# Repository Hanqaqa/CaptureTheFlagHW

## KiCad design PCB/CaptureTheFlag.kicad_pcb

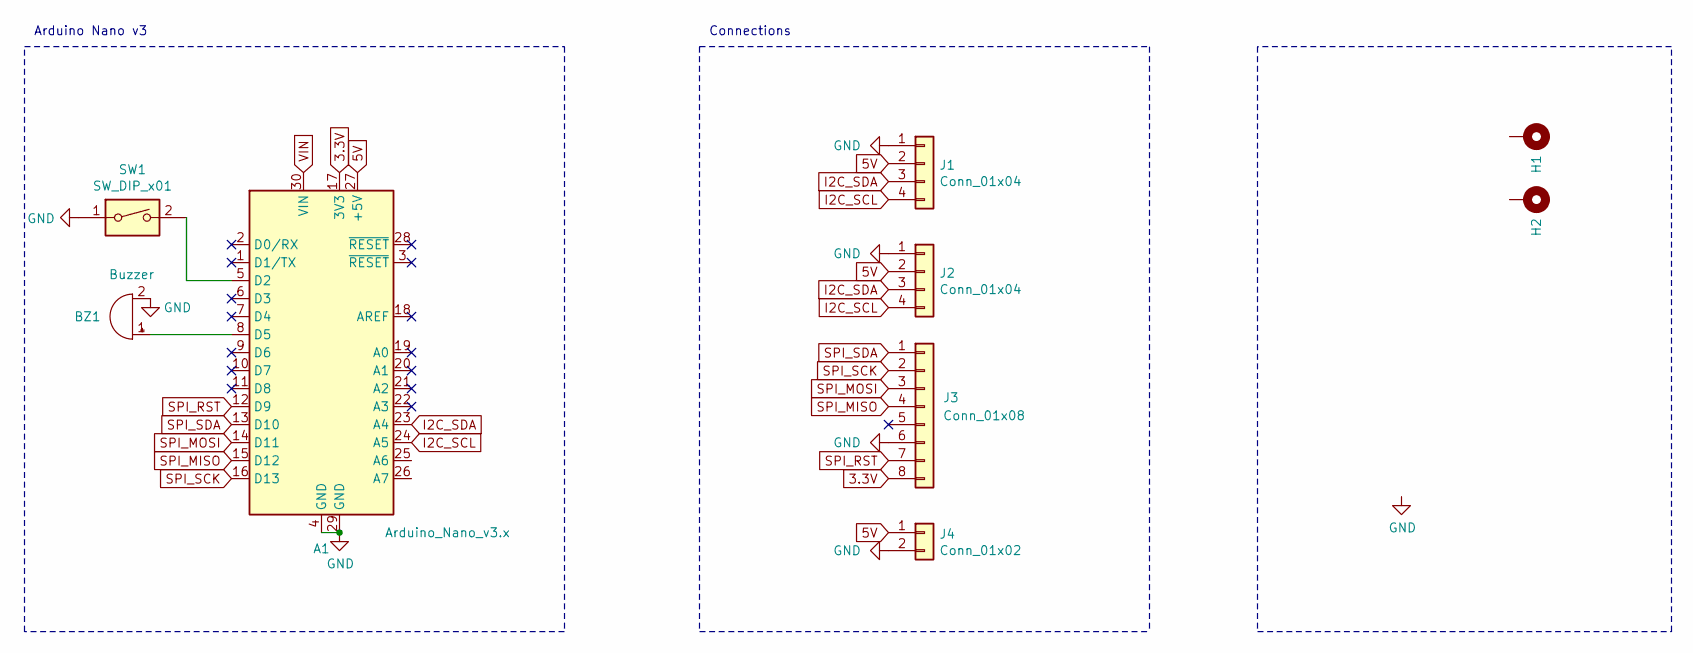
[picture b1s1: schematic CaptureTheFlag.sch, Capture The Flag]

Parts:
A1: Arduino_Nano_v3.x; Arduino_Nano
BZ1: Buzzer; Buzzer_12x9.5RM7.6
H1, H2: MountingHole_Pad; MountingHole_3.2mm_M3
J1, J2: Conn_01x04; PinHeader_1x04_P2.54mm_Vertical
J3: Conn_01x08; PinHeader_1x08_P2.54mm_Vertical
J4: Conn_01x02; PinHeader_1x02_P2.54mm_Vertical
SW1: SW_DIP_x01; PinHeader_1x02_P2.54mm_Vertical

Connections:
3.3V: A1.17 (3V3), J3.8
5V: A1.27 (+5V), J1.2, J2.2, J4.1
GND: A1.4 (GND), A1.29 (GND), BZ1.2 (+), J1.1, J2.1, J3.6, J4.2, SW1.1
I2C_SCL: A1.24 (A5), J1.4, J2.4
I2C_SDA: A1.23 (A4), J1.3, J2.3
unnamed: A1.5 (D2), SW1.2
unnamed: A1.8 (D5), BZ1.1 (-)
SPI_MISO: A1.15 (D12), J3.4
SPI_MOSI: A1.14 (D11), J3.3
SPI_RST: A1.12 (D9), J3.7
SPI_SCK: A1.16 (D13), J3.2
SPI_SDA: A1.13 (D10), J3.1
VIN: A1.30 (VIN)

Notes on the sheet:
Arduino Nano v3
Connections

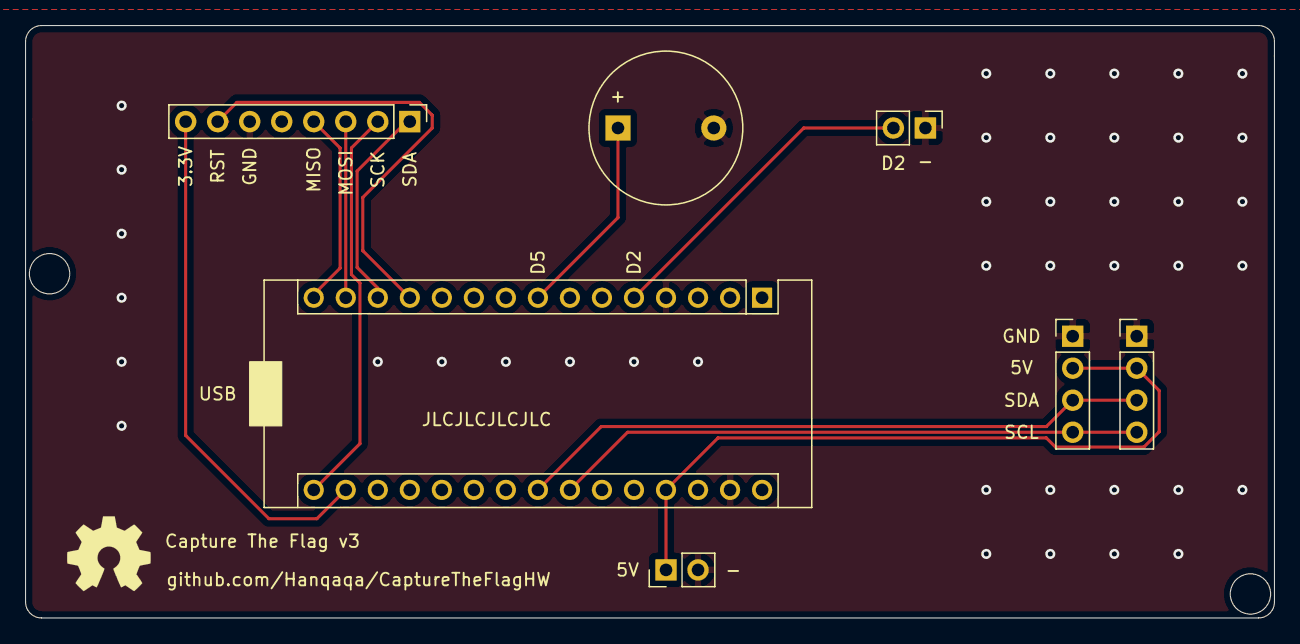
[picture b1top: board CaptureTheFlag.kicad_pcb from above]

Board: 2 copper layers, 99.1 x 47.0 mm, 9 parts (0 on the bottom side), 12 nets.

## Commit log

2020-10-15 License and readme
2021-04-25 prueba
2021-04-26 Version 1.0
2021-04-30 v1.5
2021-06-19 v2.0
2021-06-21 Added 3D box
2021-06-23 Caja parametrica
